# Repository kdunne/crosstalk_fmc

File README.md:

# crosstalk_fmc
KiCAD design files for an FPGA Mezzanine card to make bit error rate measurements of cable bundles

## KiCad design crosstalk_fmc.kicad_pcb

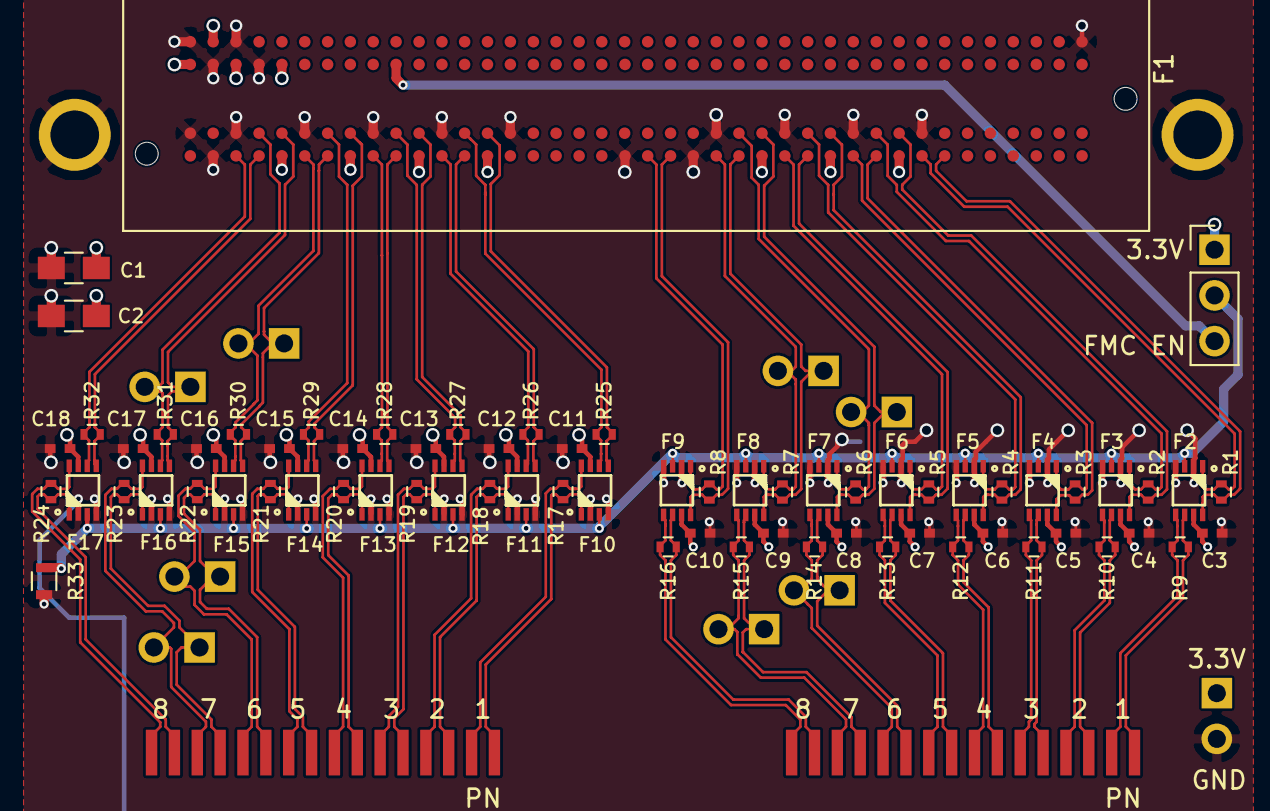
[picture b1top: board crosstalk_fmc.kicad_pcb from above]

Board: 4 copper layers, 80 parts (0 on the bottom side), 68 nets.

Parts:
C1, C2: 0.1uF; C_0805_HandSoldering
C3, C4, C5, C6, C7, C8, C9, C10, C11, C12, C13, C14, C15, C16, C17, C18: C_0402_NoSilk
F1: FMC_LPC; FMC_LPC_ASP-134604-01
F2, F3, F4, F5, F6, F7, F8, F9, F10, F11, F12, F13, F14, F15, F16, F17: F1N1101K8X; FIN1101K8X
JP1: Socket_Strip_Straight_1x03_Pitch2.54mm
R1, R2, R3, R4, R5, R6, R7, R8, R9, R10, R11, R12, R13, R14, R15, R16: R_0402
R17, R18, R19, R20, R21, R22, R23, R24, R25, R26, R27, R28, R29, R30, R31, R32: R_Small; R_0402
R33: R_0603
T1, T2: terminal
U1, U2, U3, U4, U5, U6, U7, U8, U9: data_header

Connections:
/3P3V: C1.1, C2.1, C3.1, C4.1, C5.1, C6.1, C7.1, C8.1, C9.1, C10.1, C11.1, C12.1, C13.1, C14.1, C15.1, C16.1, C17.1, C18.1, F1.C39, F1.D36, F1.D38, F1.D40, F2.7, F3.7, F4.7, F5.7, F6.7, F7.7, F8.7, F9.7, F10.7, F11.7, F12.7, F13.7, F14.7, F15.7, F16.7, F17.7, JP1.1, U9.1
/ENABLE: F2.3, F3.3, F4.3, F5.3, F6.3, F7.3, F8.3, F9.3, F10.3, F11.3, F12.3, F13.3, F14.3, F15.3, F16.3, F17.3, JP1.2, R33.1
/FMC_ENABLE: F1.D31, JP1.3
/FMC_IN_0_N: F1.G27, F10.5, R25.2
/FMC_IN_0_P: F1.G28, F10.6, R25.1
/FMC_IN_1_N: F1.H28, F11.5, R26.2
/FMC_IN_1_P: F1.H29, F11.6, R26.1
/FMC_IN_2_N: F1.G30, F12.5, R27.2
/FMC_IN_2_P: F1.G31, F12.6, R27.1
/FMC_IN_3_N: F1.H31, F13.5, R28.2
/FMC_IN_3_P: F1.H32, F13.6, R28.1
/FMC_IN_4_N: F1.G33, F14.5, R29.2
/FMC_IN_4_P: F1.G34, F14.6, R29.1
/FMC_IN_5_N: F1.H34, F15.5, R30.2, U1.1
/FMC_IN_5_P: F1.H35, F15.6, R30.1, U1.2
/FMC_IN_6_N: F1.G36, F16.5, R31.2, U5.1
/FMC_IN_6_P: F1.G37, F16.6, R31.1, U5.2
/FMC_IN_7_N: F1.H37, F17.5, R32.2
/FMC_IN_7_P: F1.H38, F17.6, R32.1
/FMC_OUT_0_N: F1.H07, F2.8, R1.2
/FMC_OUT_0_P: F1.H08, F2.1, R1.1
/FMC_OUT_1_N: F1.G09, F3.8, R2.2
/FMC_OUT_1_P: F1.G10, F3.1, R2.1
/FMC_OUT_2_N: F1.H10, F4.8, R3.2
/FMC_OUT_2_P: F1.H11, F4.1, R3.1
/FMC_OUT_3_N: F1.G12, F5.8, R4.2
/FMC_OUT_3_P: F1.G13, F5.1, R4.1
/FMC_OUT_4_N: F1.H13, F6.8, R5.2
/FMC_OUT_4_P: F1.H14, F6.1, R5.1
/FMC_OUT_5_N: F1.G15, F7.8, R6.2, U4.1
/FMC_OUT_5_P: F1.G16, F7.1, R6.1, U4.2
/FMC_OUT_6_N: F1.H16, F8.8, R7.2, U8.1
/FMC_OUT_6_P: F1.H17, F8.1, R7.1, U8.2
/FMC_OUT_7_N: F1.H19, F9.8, R8.2
/FMC_OUT_7_P: F1.H20, F9.1, R8.1
/GND: C1.2, C2.2, C3.2, C4.2, C5.2, C6.2, C7.2, C8.2, C9.2, C10.2, C11.2, C12.2, C13.2, C14.2, C15.2, C16.2, C17.2, C18.2, F1.C01, F1.C38, F1.C40, F1.D37, F1.D39, F1.G08, F1.G11, F1.G14, F1.G17, F1.G26, F1.G29, F1.G32, F1.G35, F1.G38, F1.G40, F1.H09, F1.H12, F1.H15, F1.H18, F1.H21, F1.H27, F1.H30, F1.H33, F1.H36, F1.H39, F2.2, F2.4, F3.2, F3.4, F4.2, F4.4, F5.2, F5.4, F6.2, F6.4, F7.2, F7.4, F8.2, F8.4, F9.2, F9.4, F10.2, F10.4, F11.2, F11.4, F12.2, F12.4, F13.2, F13.4, F14.2, F14.4, F15.2, F15.4, F16.2, F16.4, F17.2, F17.4, R33.2, U9.2
/TERM_IN_0_N: F2.6, R9.2, T1.1
/TERM_IN_0_P: F2.5, R9.1, T1.2
/TERM_IN_1_N: F3.6, R10.2, T1.3
/TERM_IN_1_P: F3.5, R10.1, T1.4
/TERM_IN_2_N: F4.6, R11.2, T1.5
/TERM_IN_2_P: F4.5, R11.1, T1.6
/TERM_IN_3_N: F5.6, R12.2, T1.7
/TERM_IN_3_P: F5.5, R12.1, T1.8
/TERM_IN_4_N: F6.6, R13.2, T1.9
/TERM_IN_4_P: F6.5, R13.1, T1.10
/TERM_IN_5_N: F7.6, R14.2, T1.11, U2.1
/TERM_IN_5_P: F7.5, R14.1, T1.12, U2.2
/TERM_IN_6_N: F8.6, R15.2, T1.13, U6.1
/TERM_IN_6_P: F8.5, R15.1, T1.14, U6.2
/TERM_IN_7_N: F9.6, R16.2, T1.15
/TERM_IN_7_P: F9.5, R16.1, T1.16
/TERM_OUT_0_N: F10.1, R17.2, T2.1
/TERM_OUT_0_P: F10.8, R17.1, T2.2
/TERM_OUT_1_N: F11.1, R18.2, T2.3
/TERM_OUT_1_P: F11.8, R18.1, T2.4
/TERM_OUT_2_N: F12.1, R19.2, T2.5
/TERM_OUT_2_P: F12.8, R19.1, T2.6
/TERM_OUT_3_N: F13.1, R20.2, T2.7
/TERM_OUT_3_P: F13.8, R20.1, T2.8
/TERM_OUT_4_N: F14.1, R21.2, T2.9
/TERM_OUT_4_P: F14.8, R21.1, T2.10
/TERM_OUT_5_N: F15.1, R22.2, T2.11, U3.1
/TERM_OUT_5_P: F15.8, R22.1, T2.12, U3.2
/TERM_OUT_6_N: F16.1, R23.2, T2.13, U7.1
/TERM_OUT_6_P: F16.8, R23.1, T2.14, U7.2
/TERM_OUT_7_N: F17.1, R24.2, T2.15
/TERM_OUT_7_P: F17.8, R24.1, T2.16

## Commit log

2017-12-07 Initialize repository
2017-12-10 Replace buffers, add termination on both sides
2018-01-26 Add shield pads, switch for buff enable
2018-02-11 Add logo, final version
2018-02-11 Add readme.md
